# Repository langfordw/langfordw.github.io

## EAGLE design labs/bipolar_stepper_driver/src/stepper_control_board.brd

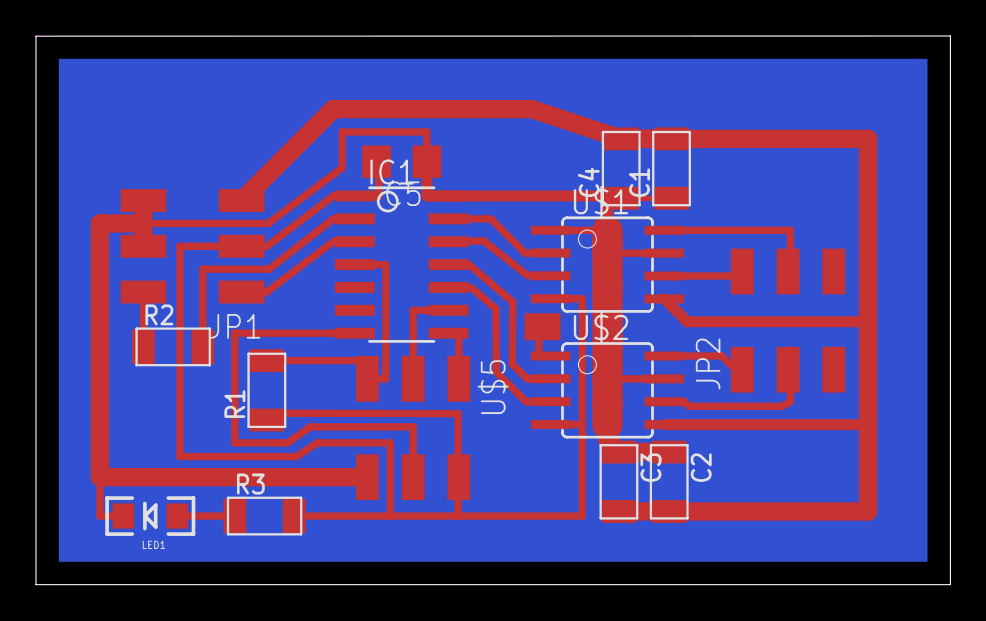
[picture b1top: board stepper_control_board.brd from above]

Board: 2 copper layers, 50.8 x 30.5 mm, 16 parts (0 on the bottom side), 18 nets.

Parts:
C1, C2: .1uF; C1206FAB
C3, C4: 10uF; C1206FAB
C5: C1206
IC1: ATTINY44-SSU; SOIC14
JP1, JP2: 2X03SMD
JP3: M01SMD-4.5X1.5; PAD-1.5X4.5
LED1: LED-1206
R1: 10K; R1206FAB
R2: 0; R1206FAB
R3: 100; R1206FAB
U$1, U$2: A4953-H-BRIDGE-MOTOR-DRIVER; SOIC8
U$5: AVRISPSMD; 2X03SMD

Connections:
5V: C5.2, IC1.1, JP1.3, R1.1, R3.2, U$1.4, U$2.4, U$5.2
DIR: IC1.2, JP1.2, R2.1, R2.2
GND: C1.1, C2.1, C3.1, C4.1, C5.1, IC1.14, JP1.4, JP1.6, JP3.P$1, LED1.C, U$1.1, U$1.7, U$2.1, U$2.7, U$5.6
IN1: IC1.12, U$1.3
IN2: IC1.13, U$1.2
IN3: IC1.10, U$2.3
IN4: IC1.11, U$2.2
MISO: IC1.8, U$5.1
MOSI: IC1.7, U$5.4
unnamed: JP2.1, U$2.8
unnamed: JP2.3, U$2.6
unnamed: JP2.4, U$1.8
unnamed: LED1.A, R3.1
unnamed: JP2.2, U$1.6
RESET: IC1.4, R1.2, U$5.5
SCK: IC1.9, U$5.3
STEP: IC1.3, JP1.1
V+: C1.2, C2.2, C3.2, C4.2, JP1.5, U$1.5, U$2.5

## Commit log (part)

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2015-05-14 init
2015-05-14 Create CNAME
2015-05-14 Update CNAME
2015-09-25 test change
2016-05-22 adding website
2016-05-22 fixed caps
2016-05-22 adding micropillars and fablab armenia
2016-05-23 adding rwanda pics
2016-06-16 adding image dimension extractor
2016-06-16 fixing
2016-06-16 removing
2016-07-11 adding msec presentation
2016-07-11 fixed presentation
2016-07-11 added subsections
2016-07-11 adding index to pres
2016-07-11 adding tardis
2016-07-11 adding merck pres
2016-07-11 small change
2016-07-11 adding old presentations
2016-07-11 adding new projects
2016-07-11 adding fdm presentation
2016-07-12 adding python packandgo script
2016-07-13 adding cba overview pres
2016-07-13 fixing cba
2016-07-13 fixing cba2
2016-07-20 fixed digicam bug?
2016-08-09 adding voice coil designer
2016-08-22 adding lattice designer
2016-08-22 change link
2016-09-28 updating 5.0x magnification
2016-12-09 adding mechanism simulator
2016-12-23 fixing google analytics
2016-12-30 website update
2018-05-30 adding mechsim and stapler
2018-05-30 add back button2
2018-05-30 update stapler pic
2018-06-04 adding instron and popup image
2018-06-10 add dwedm
2018-06-10 add fablab bhutan
2018-06-10 small fix
2018-06-10 add cubesat
2019-01-07 update resume
2019-01-07 fix about
2019-01-07 fix ta'ing
2019-02-26 adding walking motor
2019-02-26 remove next steps
2019-02-26 add strapdown
2019-02-26 add style
2019-02-26 adding automating assembly
2019-02-26 adding screenshot
2019-05-27 fix mechsim paper link
2019-05-27 update resume with mrmss paper
2019-09-04 updaing resume
2019-09-04 fix bloombot link
2023-03-19 basic new site
2023-03-19 basic about page
2023-03-20 snapshot in development on about page
2023-03-24 major reorg
2023-03-28 add venn diagram
2023-03-28 more work on venn
2023-03-28 fix autoscroll
2023-03-29 minor changes
2023-03-31 handlebar working, arrows functional
2023-04-03 added list of projects & working next and previous
2023-04-03 added timeline
2023-04-03 fix index
2023-04-03 add timeline, refactor content delivery, add nav
    Squashed commit of the following:
    commit 72749b99fa46b17b52fcaca155eb643b826f7507
    Author: Will Langford <langfordw@gmail.com>
    Date: Mon Apr 3 13:37:21 2023 -0400
    fix index
    commit 6bfd86cb26dda18a119e0084506b495b16a36cff
2023-04-25 mostly finished content
2023-04-25 fix capitalization
2023-04-26 massive cleanup
2023-05-02 open cv in new tab
2023-05-12 add google analytics
2023-06-27 updated resume with about section
